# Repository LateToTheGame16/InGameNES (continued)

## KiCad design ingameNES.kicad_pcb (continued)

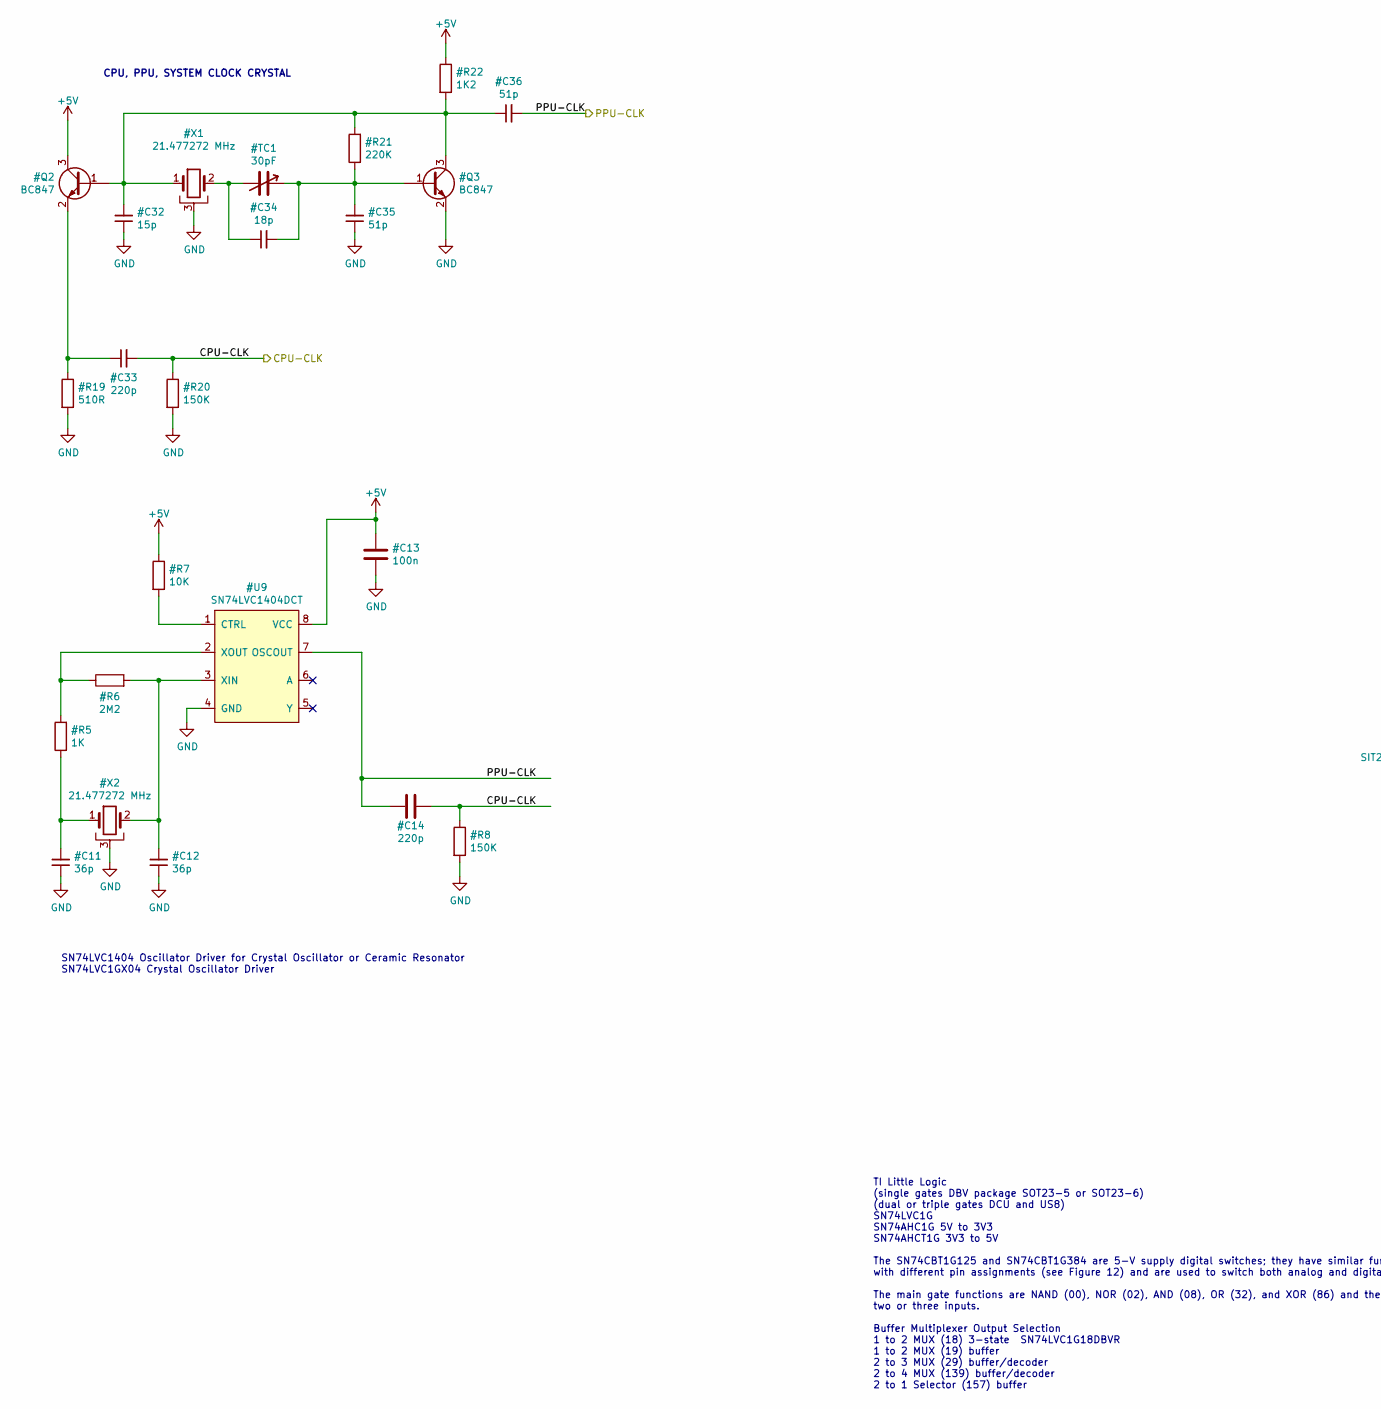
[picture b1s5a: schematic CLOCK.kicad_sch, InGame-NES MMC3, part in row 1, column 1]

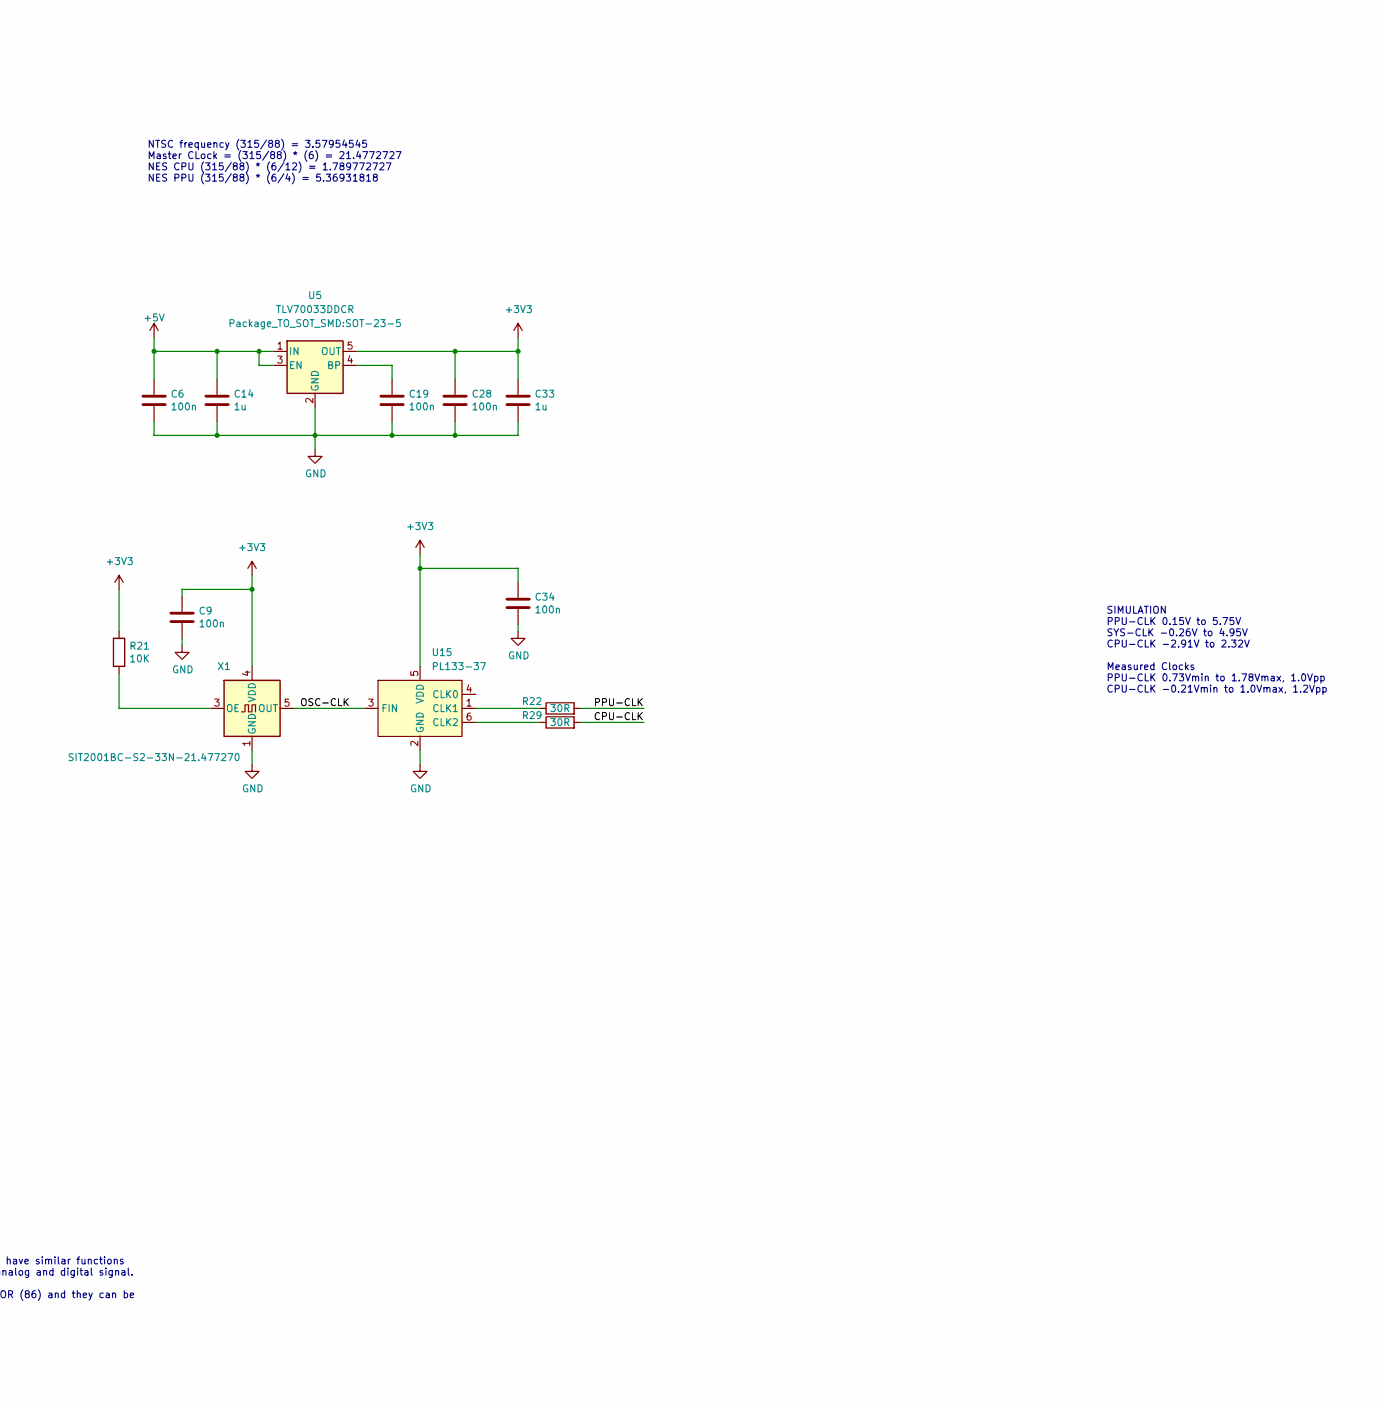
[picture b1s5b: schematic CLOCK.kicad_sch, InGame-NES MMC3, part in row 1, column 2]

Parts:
C6, C9, C19, C28, C34: 100n; C_0402_1005Metric; MPN CL05B104KO5NNWC; Digikey 1276-1509-2-ND
C14, C33: 1u; C_0402_1005Metric; MPN GRM155R61A105KE15D; Digikey 490-3890-2-ND
R21: 10K; R_0402_1005Metric; MPN ERJ-2RKF1002X; Digikey P10.0KLCT-ND
R22, R29: 30R; R_0402_1005Metric; MPN RC0402JR-0730RL; Digikey 311-30JRCT-ND
U5: TLV70033DDCR; SOT-23-5; MPN TLV70033DDCR; Digikey 296-27937-1-ND
U15: PL133-37; SOT-23-6; MPN PL133-37TC; Digikey 576-5036-5-ND
X1: SIT2001BC-S2-33N-21.477270; SOT-23-5; MPN SIT2001BC-S2-33N-21.477270; Digikey 1473-SIT2001BC-S2-33N-21.477270-ND

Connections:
+3V3: C9.2, C28.2, C33.2, C34.2, R21.1, U5.5 (OUT), U15.5 (VDD), X1.4 (VDD)
/TIMING/OSC-CLK: U15.3 (FIN), X1.5 (OUT)
unnamed: C19.2, U5.4 (BP)
unnamed: R21.2, X1.3 (OE)
unnamed: R22.1, U15.1 (CLK1)
unnamed: R29.1, U15.6 (CLK2)

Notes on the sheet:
SIMULATION PPU-CLK 0.15V to 5.75V SYS-CLK -0.26V to 4.95V CPU-CLK -2.91V to 2.32V Measured Clocks PPU-CLK 0.73Vmin to 1.78Vmax, 1.0Vpp CPU-CLK -0.21Vmin to 1.0Vmax, 1.2Vpp
TI Little Logic (single gates DBV package SOT23-5 or SOT23-6) (dual or triple gates DCU and US8) SN74LVC1G SN74AHC1G 5V to 3V3 SN74AHCT1G 3V3 to 5V The SN74CBT1G125 and SN74CBT1G384 are 5-V supply digital switches; they have similar functions with different pin assignments (see Figure 12) and are u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
CPU, PPU, SYSTEM CLOCK CRYSTAL
NTSC frequency (315/88) = 3.57954545 Master CLock = (315/88) * (6) = 21.4772727 NES CPU (315/88) * (6/12) = 1.789772727 NES PPU (315/88) * (6/4) = 5.36931818
SN74LVC1404 Oscillator Driver for Crystal Oscillator or Ceramic Resonator SN74LVC1GX04 Crystal Oscillator Driver

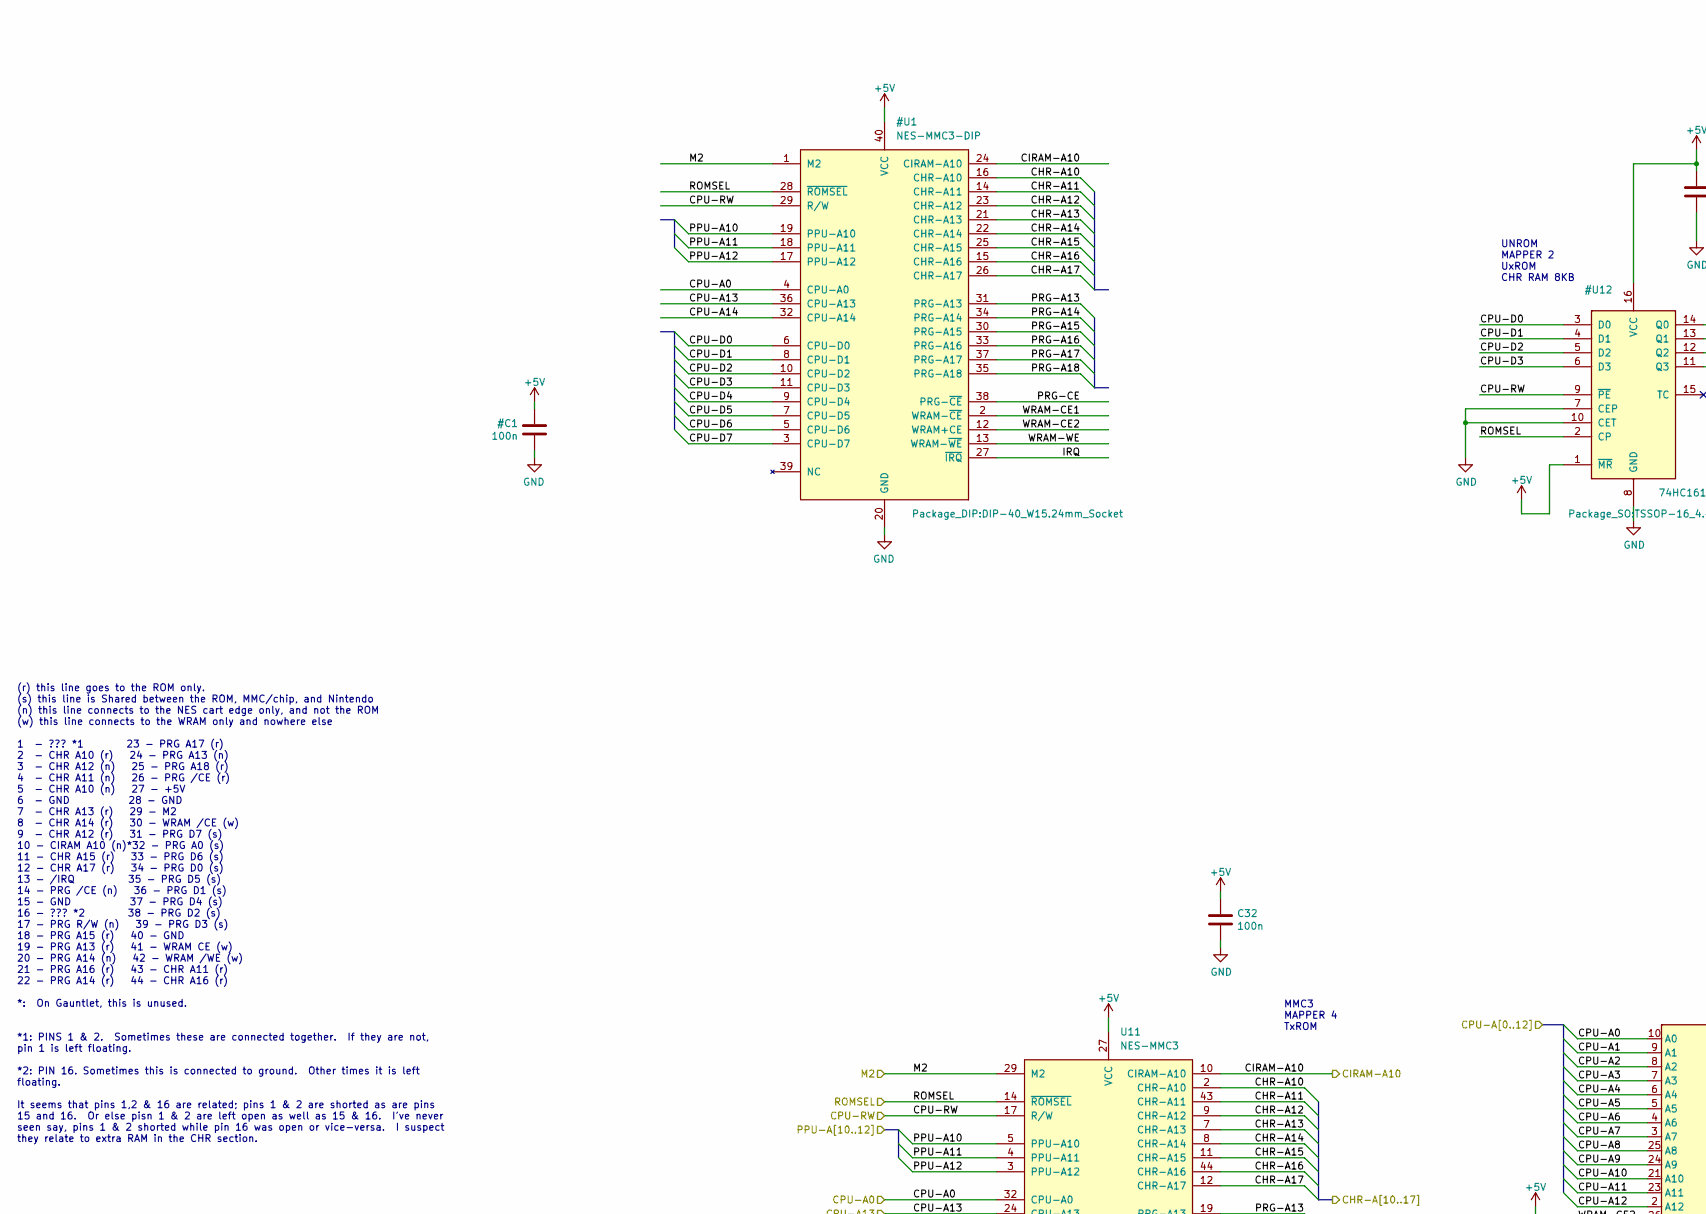
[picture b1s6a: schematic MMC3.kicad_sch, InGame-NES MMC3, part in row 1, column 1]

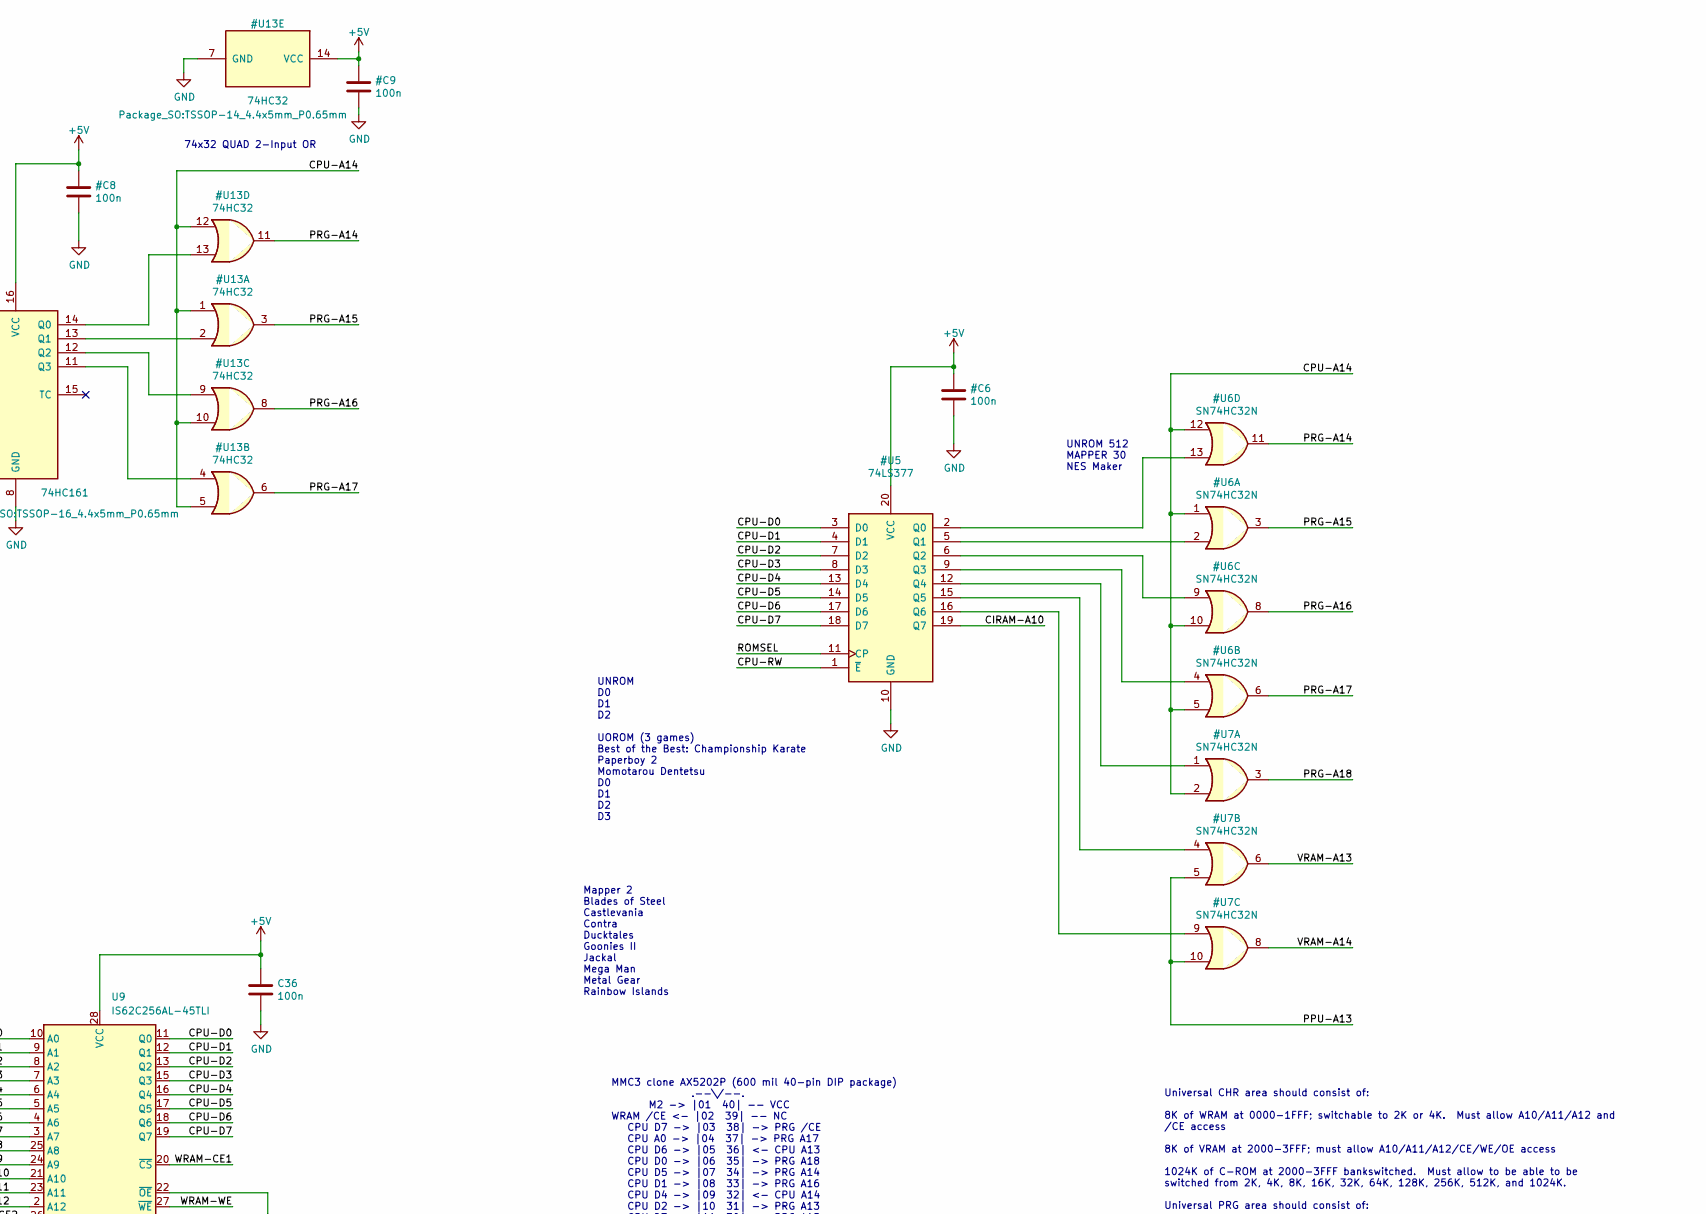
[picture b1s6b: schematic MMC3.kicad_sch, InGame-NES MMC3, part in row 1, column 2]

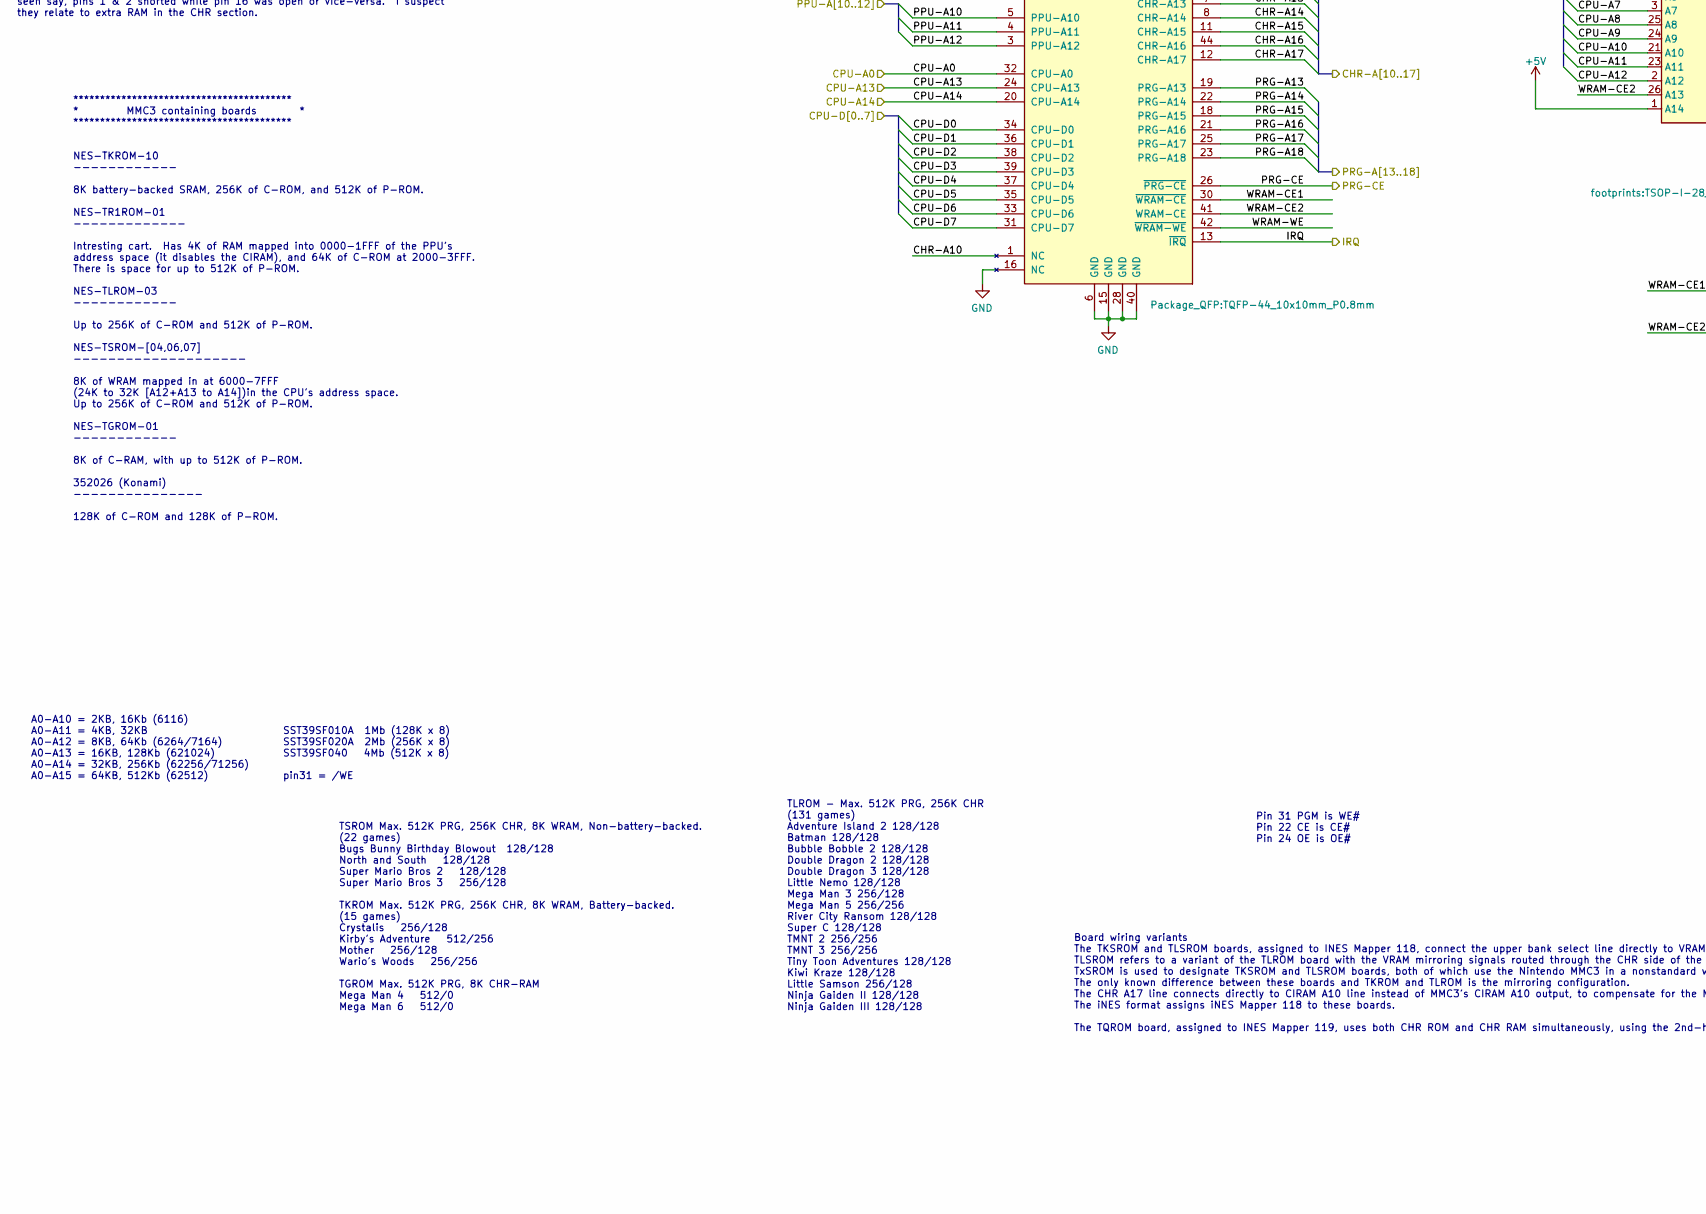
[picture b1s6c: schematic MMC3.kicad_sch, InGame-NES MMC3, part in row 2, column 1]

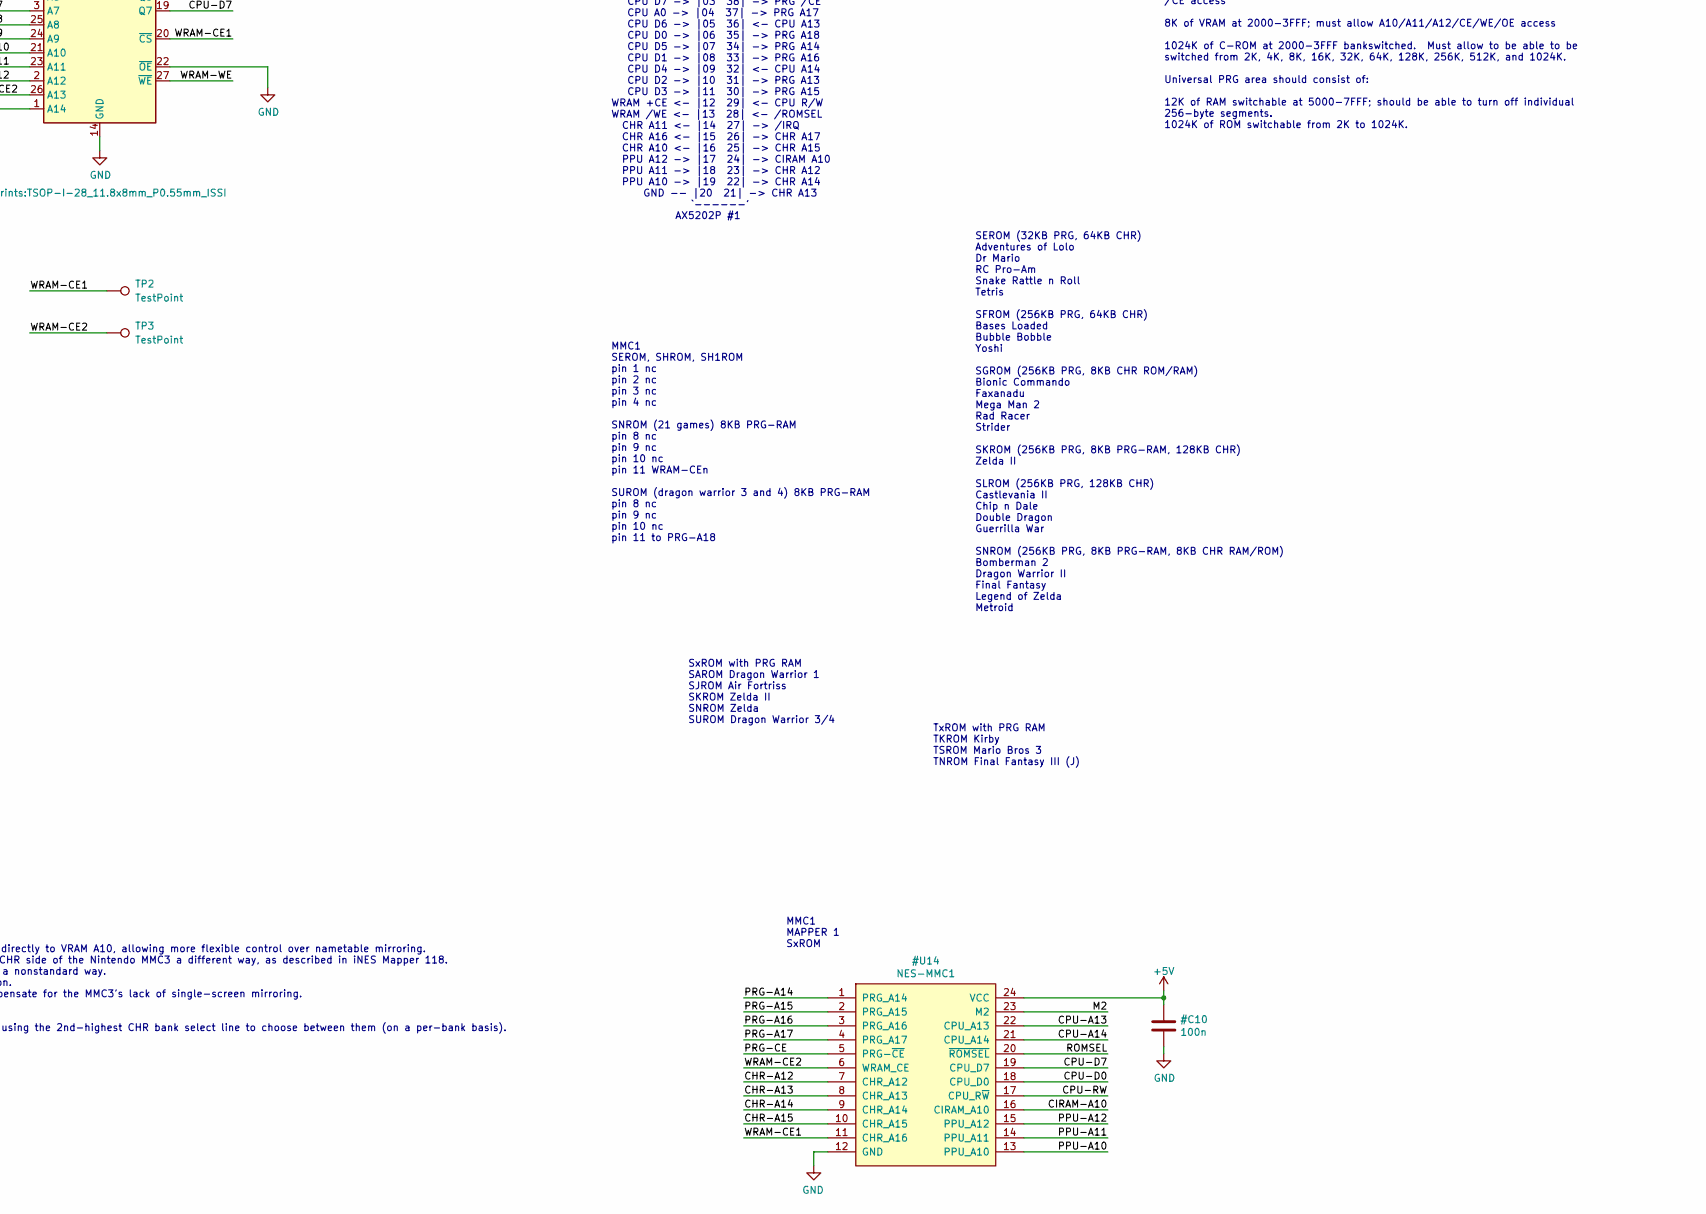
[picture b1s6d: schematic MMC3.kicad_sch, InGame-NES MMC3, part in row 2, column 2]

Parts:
C32, C36: 100n; C_0402_1005Metric; MPN CL05B104KO5NNWC; Digikey 1276-1509-2-ND
TP2, TP3: TestPoint; TestPoint_Pad_D1.5mm
U9: IS62C256AL-45TLI; TSOP-I-28_11.8x8mm_P0.55mm_ISSI; MPN IS62C256AL-45TLI; Digikey 706-1109-ND
U11: NES-MMC3; TQFP-44_10x10mm_P0.8mm

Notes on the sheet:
SxROM with PRG RAM SAROM Dragon Warrior 1 SJROM Air Fortriss SKROM Zelda II SNROM Zelda SUROM Dragon Warrior 3/4
MMC1 SEROM, SHROM, SH1ROM pin 1 nc pin 2 nc pin 3 nc pin 4 nc SNROM (21 games) 8KB PRG-RAM pin 8 nc pin 9 nc pin 10 nc pin 11 WRAM-CEn SUROM (dragon warrior 3 and 4) 8KB PRG-RAM pin 8 nc pin 9 nc pin 10 nc pin 11 to PRG-A18
A0-A10 = 2KB, 16Kb (6116) A0-A11 = 4KB, 32KB A0-A12 = 8KB, 64Kb (6264/7164) A0-A13 = 16KB, 128Kb (621024) A0-A14 = 32KB, 256Kb (62256/71256) A0-A15 = 64KB, 512Kb (62512)
Universal CHR area should consist of: 8K of WRAM at 0000-1FFF; switchable to 2K or 4K. Must allow A10/A11/A12 and /CE access 8K of VRAM at 2000-3FFF; must allow A10/A11/A12/CE/WE/OE access 1024K of C-ROM at 2000-3FFF bankswitched. Must allow to be able to be switched from 2K, 4K, 8K, 16K, 32K, 64K,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
MMC3 clone AX5202P (600 mil 40-pin DIP package) .--\/--. M2 -> |01 40| -- VCC WRAM /CE <- |02 39| -- NC CPU D7 -> |03 38| -> PRG /CE CPU A0 -> |04 37| -> PRG A17 CPU D6 -> |05 36| <- CPU A13 CPU D0 -> |06 35| -> PRG A18 CPU D5 -> |07 34| -> PRG A14 CPU D1 -> |08 33| -> PRG A16 CPU D4 -> |09 32| <- 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
UNROM MAPPER 2 UxROM CHR RAM 8KB
SEROM (32KB PRG, 64KB CHR) Adventures of Lolo Dr Mario RC Pro-Am Snake Rattle n Roll Tetris SFROM (256KB PRG, 64KB CHR) Bases Loaded Bubble Bobble Yoshi SGROM (256KB PRG, 8KB CHR ROM/RAM) Bionic Commando Faxanadu Mega Man 2 Rad Racer Strider SKROM (256KB PRG, 8KB PRG-RAM, 128KB CHR) Zelda II SLROM 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
UNROM 512 MAPPER 30 NES Maker
TSROM Max. 512K PRG, 256K CHR, 8K WRAM, Non-battery-backed. (22 games) Bugs Bunny Birthday Blowout 128/128 North and South 128/128 Super Mario Bros 2 128/128 Super Mario Bros 3 256/128 TKROM Max. 512K PRG, 256K CHR, 8K WRAM, Battery-backed. (15 games) Crystalis 256/128 Kirby's Adventure 512/256 Mot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
TLROM - Max. 512K PRG, 256K CHR (131 games) Adventure Island 2 128/128 Batman 128/128 Bubble Bobble 2 128/128 Double Dragon 2 128/128 Double Dragon 3 128/128 Little Nemo 128/128 Mega Man 3 256/128 Mega Man 5 256/256 River City Ransom 128/128 Super C 128/128 TMNT 2 256/256 TMNT 3 256/256 Tiny Toon A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
MMC3 MAPPER 4 TxROM
TxROM with PRG RAM TKROM Kirby TSROM Mario Bros 3 TNROM Final Fantasy III (J)
SST39SF010A 1Mb (128K x 8) SST39SF020A 2Mb (256K x 8) SST39SF040 4Mb (512K x 8) pin31 = /WE
(r) this line goes to the ROM only. (s) this line is Shared between the ROM, MMC/chip, and Nintendo (n) this line connects to the NES cart edge only, and not the ROM (w) this line connects to the WRAM only and nowhere else 1 - ??? *1 23 - PRG A17 (r) 2 - CHR A10 (r) 24 - PRG A13 (n) 3 - CHR A12 (n)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
74x32 QUAD 2-Input OR
Pin 31 PGM is WE# Pin 22 CE is CE# Pin 24 OE is OE#
Mapper 2 Blades of Steel Castlevania Contra Ducktales Goonies II Jackal Mega Man Metal Gear Rainbow Islands
***************************************** * MMC3 containing boards * ***************************************** NES-TKROM-10 ------------ 8K battery-backed SRAM, 256K of C-ROM, and 512K of P-ROM. NES-TR1ROM-01 ------------- Intresting cart. Has 4K of RAM mapped into 0000-1FFF of the PPU's address sp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
Board wiring variants The TKSROM and TLSROM boards, assigned to INES Mapper 118, connect the upper bank select line directly to VRAM A10, allowing more flexible control over nametable mirroring. TLSROM refers to a variant of the TLROM board with the VRAM mirroring signals routed through the CHR sid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
MMC1 MAPPER 1 SxROM
UNROM D0 D1 D2 UOROM (3 games) Best of the Best: Championship Karate Paperboy 2 Momotarou Dentetsu D0 D1 D2 D3

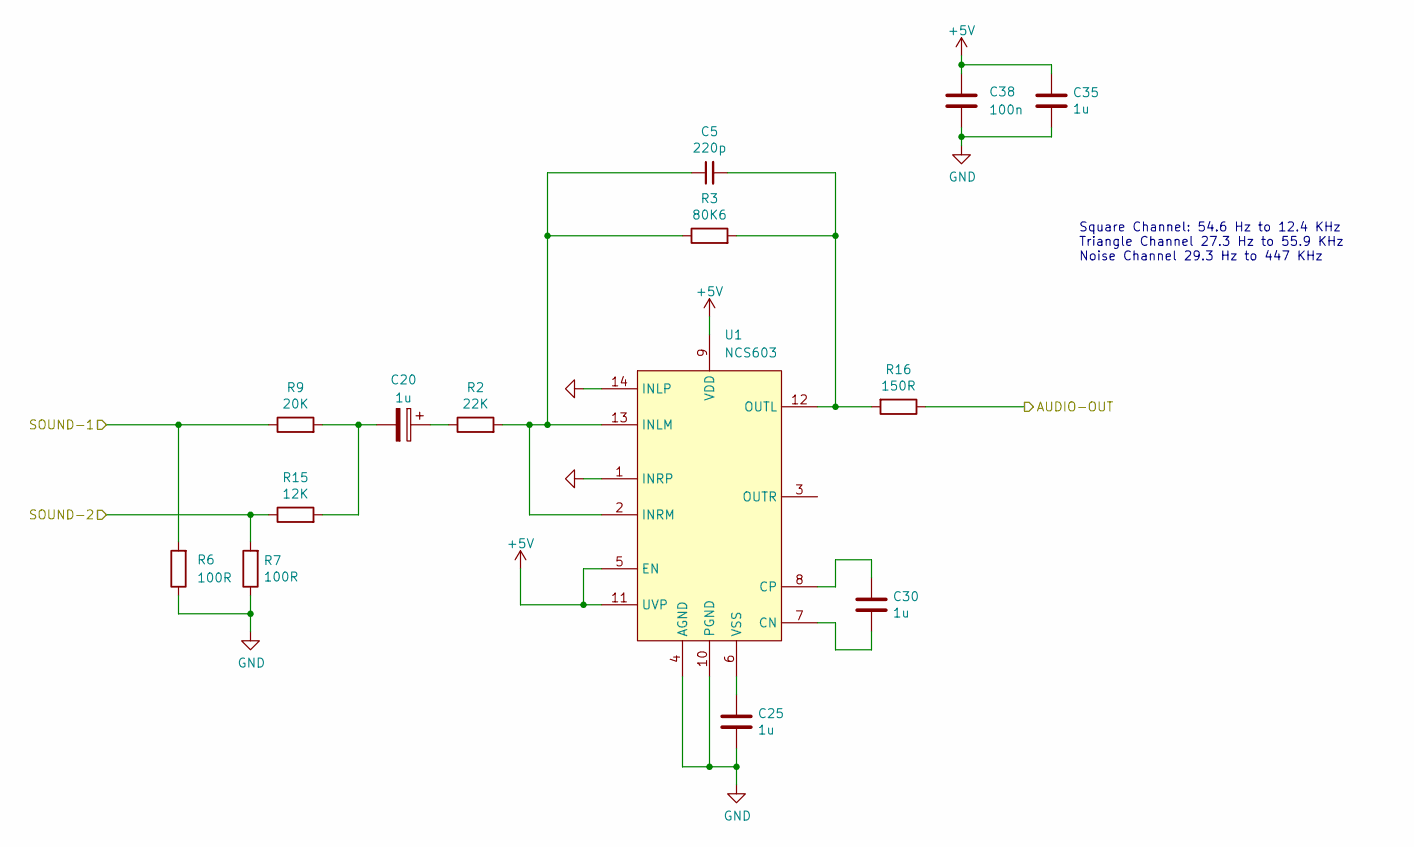
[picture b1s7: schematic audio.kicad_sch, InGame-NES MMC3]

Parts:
C5: 220p; C_0402_1005Metric; MPN CL05C221JB5NNNC; Digikey 1276-1059-1-ND
C20, C25, C30, C35: 1u; C_0402_1005Metric; MPN GRM155R61A105KE15D; Digikey 490-3890-2-ND
C38: 100n; C_0402_1005Metric; MPN CL05B104KO5NNWC; Digikey 1276-1509-2-ND
R2: 22K; R_0402_1005Metric; MPN RC0402FR-0722KL; Digikey 311-22.0KLRCT-ND
R3: 80K6; R_0402_1005Metric; MPN RC0402FR-0780K6L; Digikey 311-80.6KLRCT-ND
R6, R7: 100R; R_0402_1005Metric; MPN ERJ-2RKF1000X; Digikey P100LCT-ND
R9: 20K; R_0402_1005Metric; MPN RR0510P-203-D; Digikey RR05P20.0KDCT-ND
R15: 12K; R_0402_1005Metric; MPN RC0402FR-1312KL; Digikey 13-RC0402FR-1312KLCT-ND
R16: 150R; R_0603_1608Metric; MPN RC0603FR-07150RL; Digikey 311-150HRCT-ND
U1: NCS603; TSSOP-14_4.4x5mm_P0.65mm; MPN NCS603DTBR2G; Digikey NCS603DTBR2GOSCT-ND

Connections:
/AUDIO-OUT: R16.1; also elsewhere on the board
/Audio/SOUND-1: R6.2, R9.1; also elsewhere on the board
/Audio/SOUND-2: R7.2, R15.1; also elsewhere on the board
unnamed: C5.1, R2.2, R3.1, U1.2 (INRM), U1.13 (INLM)
unnamed: C5.2, R3.2, R16.2, U1.12 (OUTL)
unnamed: C20.1, R2.1
unnamed: C20.2, R9.2, R15.2
unnamed: C25.2, U1.6 (VSS)
unnamed: C30.1, U1.7 (CN)
unnamed: C30.2, U1.8 (CP)

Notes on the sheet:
Square Channel: 54.6 Hz to 12.4 KHz Triangle Channel 27.3 Hz to 55.9 KHz Noise Channel 29.3 Hz to 447 KHz

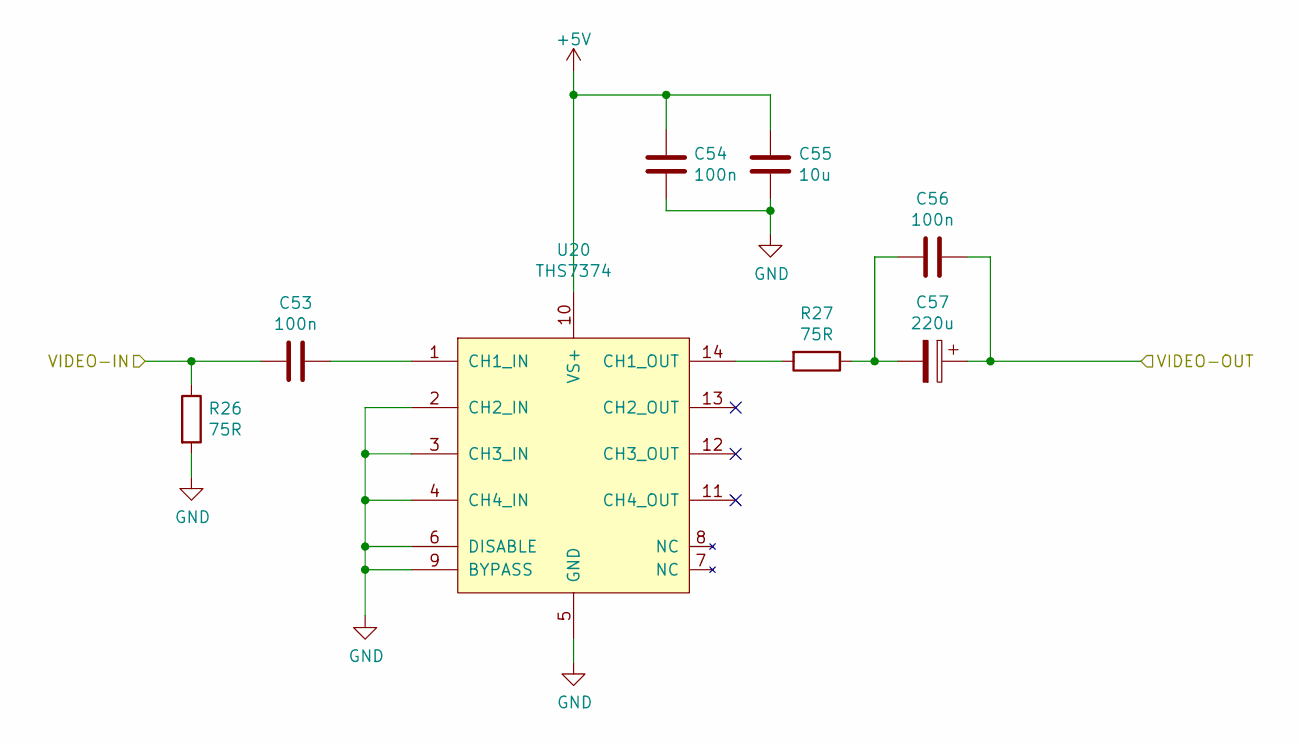
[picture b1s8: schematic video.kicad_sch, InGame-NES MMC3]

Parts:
C53, C54, C56: 100n; C_0402_1005Metric; MPN CL05B104KO5NNWC; Digikey 1276-1509-2-ND
C55: 10u; C_0805_2012Metric; MPN C0805C106K8PACTU; Digikey 399-4925-1-ND
C57: 220u; CP_EIA-7343-15_Kemet-W; MPN 593D227X9010D2TE3; Digikey 718-1105-1-ND
R26, R27: 75R; R_0402_1005Metric; MPN ERJ-2RKF75R0X; Digikey P75.0LCT-ND
U20: THS7374; TSSOP-14_4.4x5mm_P0.65mm; MPN THS7374IPWR; Digikey 296-41661-1-ND

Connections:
/PPU/VIDEO: C53.2, R26.1; also elsewhere on the board
/VIDEO-OUT: C56.1, C57.1; also elsewhere on the board
unnamed: C53.1, U20.1 (CH1_IN)
unnamed: C56.2, C57.2, R27.1
unnamed: R27.2, U20.14 (CH1_OUT)

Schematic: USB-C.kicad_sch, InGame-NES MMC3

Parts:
C1, C2: 330p; C_0402_1005Metric; MPN 0402N331J500CT; Digikey 1292-1308-1-ND
C3, C4: 10u; C_0805_2012Metric; MPN C0805C106K8PACTU; Digikey 399-4925-1-ND
D3: SMAJ22CA; D_SMA; MPN P4SMAJ22CAS_R1_00001; Digikey 3757-P4SMAJ22CAS_R1_00001CT-ND
D4: PESD2IVN24-TR; SOT-23; MPN DESD2CAN2SOQ-7; Digikey DESD2CAN2SOQ-7DICT-ND
J2: UJC-HP-3-SMT-TR; USB_C_Receptacle_CUI_UJC-HP-3-SMT-TR; MPN UJC-HP-3-SMT-TR; Digikey 2223-UJC-HP-3-SMT-CT-ND
R4, R20: 5K1; R_0402_1005Metric; MPN RC0402FR-075K1L; Digikey 311-5.10KLRCT-ND

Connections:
/USB-C-POWER/CC1: C2.1, D4.2 (K), J2.A5 (CC1), R20.1
/USB-C-POWER/CC2: C1.1, D4.1 (K), J2.B5 (CC2), R4.1

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
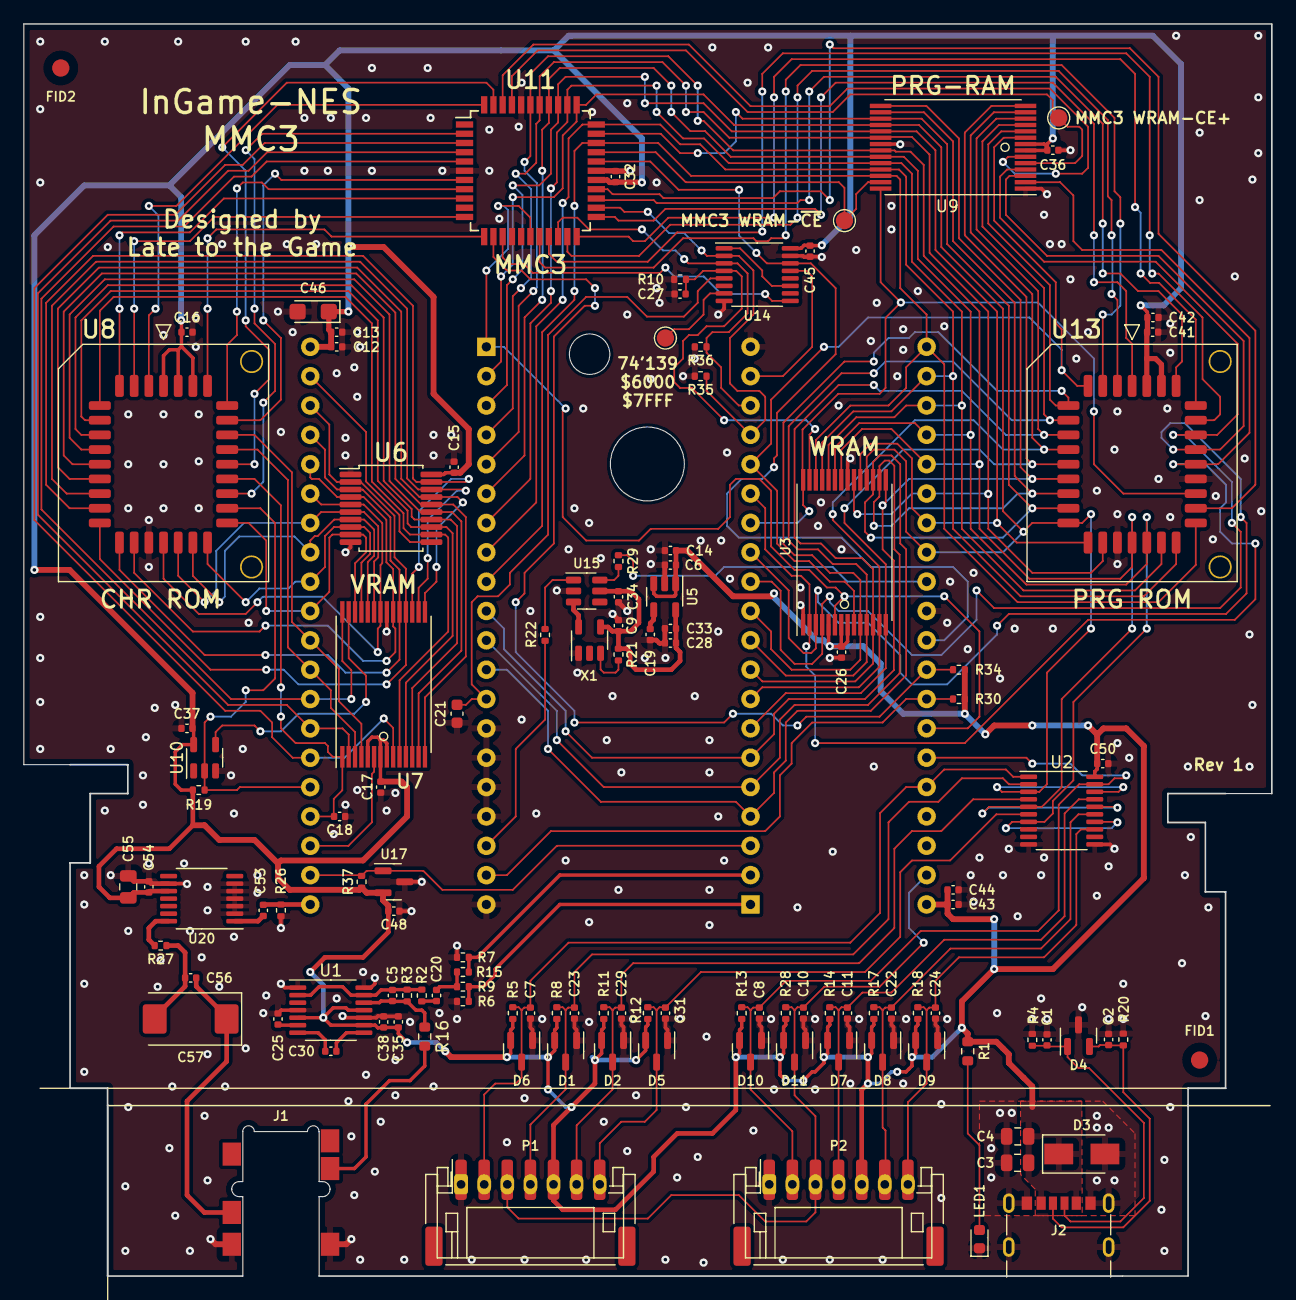
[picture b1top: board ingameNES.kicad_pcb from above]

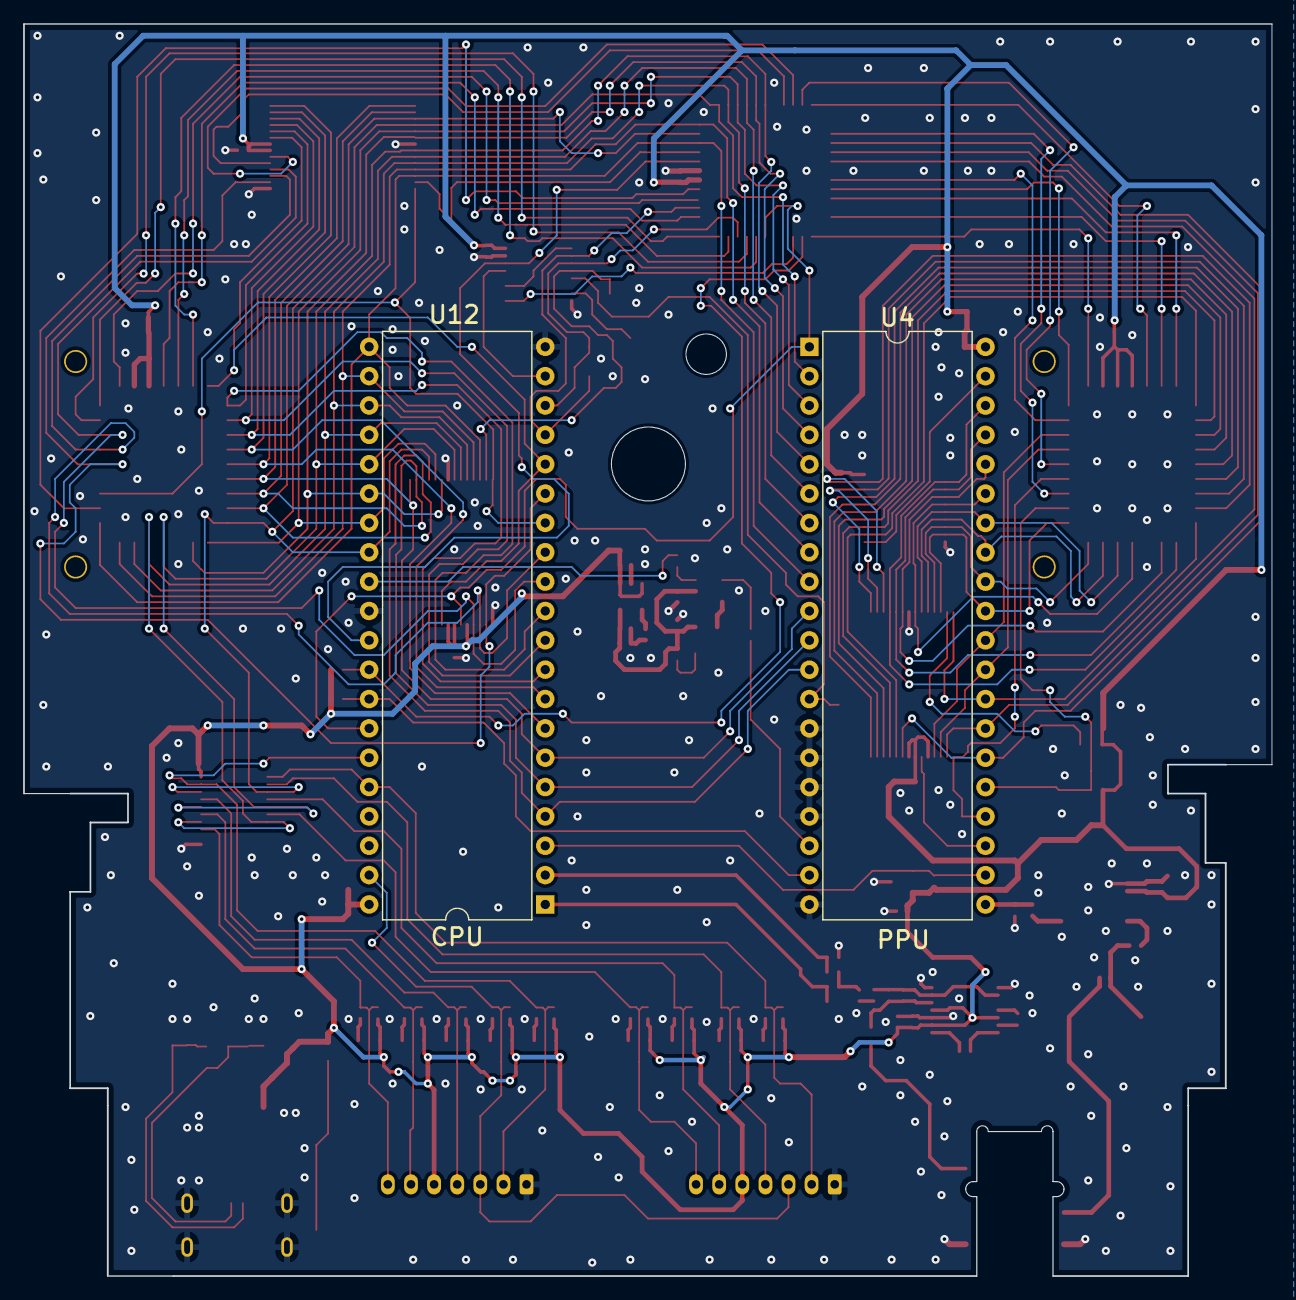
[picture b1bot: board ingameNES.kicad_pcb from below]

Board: 2 copper layers, 108.0 x 108.3 mm, 125 parts (2 on the bottom side), 115 nets.

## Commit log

2022-06-28 first fab sent out
2022-07-29 rev2 sent to fab
    Added CHR RAM.
    Changed board to 4 layers (was 2 layers).
    Changed passives to 0603 (was 0402)
    Fixed CIRAM-A10 not being hooked up
    Fixed PPU-A10..A12 being hooked to VRAM but should have been.
    Added more silkscreen for easier debugging.
2022-08-04 filled out BOM
2022-08-10 InGameNES rev 2.1
    Change AV pinout to CTIA standard. Mono audio goes to R and L channels. Video now pinned to sleeve so its yellow on 3RCA breakout.
    -Added boundary rule so copper fills do not bridge pins. The bridges were on SRAM near capacitors. It is electrically correct but it looks wrong for QA.
